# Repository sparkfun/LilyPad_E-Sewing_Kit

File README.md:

Lilypad E-Sewing ProtoSnap
====================

<table class="table table-hover table-striped table-bordered">
  <tr>
   <td><a href="https://www.sparkfun.com/products/14546"><div align="center"></div></a></center></td>
   <td><a href="https://www.sparkfun.com/products/14528"><div align="center"></div></a></td>
  </tr>
  <tr>
    <td><div align="center">LilyPad E-Sewing ProtoSnap [<a href="https://www.sparkfun.com/products/14546">DEV-14546</a>]</div></td>
    <td><div align="center">LilyPad E-Sewing ProtoSnap Kit [<a href="https://www.sparkfun.com/products/14528">KIT-14528</a>]</div></td>
  </tr>
</table>

The LilyPad E-Sewing ProtoSnap is a great way to explore how buttons and switches behave in simple e-sewing circuits before crafting your project. It comes pre-wired so you can plug in a battery and use the switch and button to turn the LEDs on and off. 

Repository Contents
-------------------
* **/Hardware** - All Eagle design files (.brd, .sch)
* **/Production** - Production panel files (.brd)

Documentation
--------------
* **[Hookup Guide](https://learn.sparkfun.com/tutorials/lilypad-e-sewing-protosnap-hookup-guide)** - Basic hookup guide for the E-Sewing ProtoSnap.

Version History
---------------
* [Hw-v15](https://github.com/sparkfun/LilyPad_E-Sewing_Kit/releases/tag/Hw-v15) - Version 15. Currently available.
* [Hw-v13](https://github.com/sparkfun/LilyPad_E-Sewing_Kit/releases/tag/Hw-v13) - Version 13. (Retired)

Product Versions
----------------
* [DEV-14546](https://www.sparkfun.com/products/14546) - LilyPad E-Sewing ProtoSnap
* [KIT-14528](https://www.sparkfun.com/products/14528) - LilyPad E-Sewing ProtoSnap Kit
* [DEV-11032](https://www.sparkfun.com/products/11032) - ProtoSnap LilyPad E-Sewing Kit (v13 Retired)
* [RTL-11051](https://www.sparkfun.com/products/11051) - Retail packaging of LilyPad E-Sewing Kit (Retired)
* [DEV-10964](https://www.sparkfun.com/products/retired/10964) - ProtoSnap - LilyPad E-Sewing Kit (v11 Retired)

License Information
-------------------
The hardware is released under [Creative Commons Share-alike 3.0](http://creativecommons.org/licenses/by-sa/3.0/).

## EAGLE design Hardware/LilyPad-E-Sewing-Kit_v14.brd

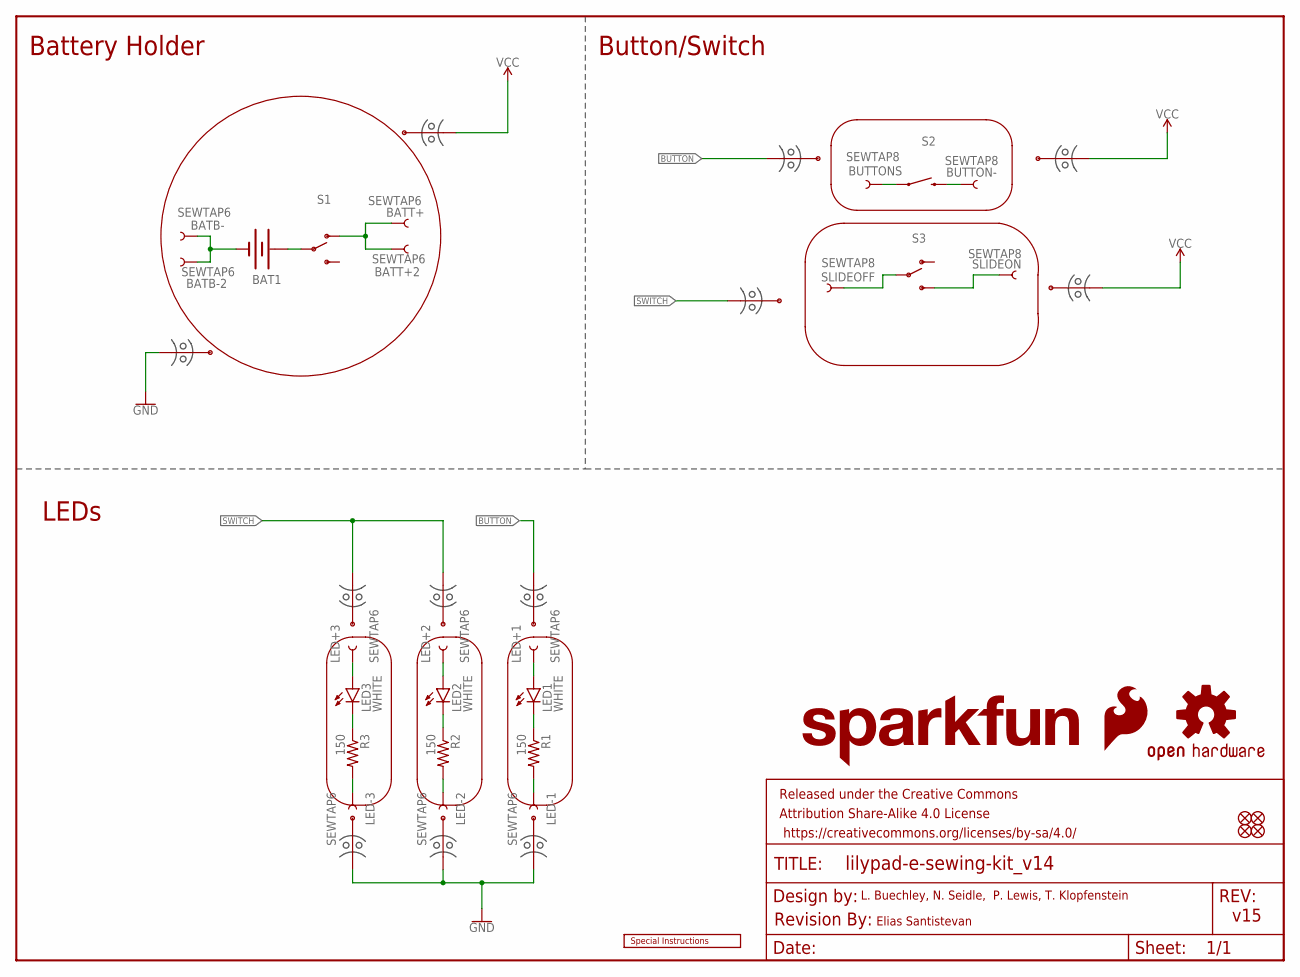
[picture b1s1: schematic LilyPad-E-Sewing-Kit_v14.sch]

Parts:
BAT1: 20mm coincell; BATTCON_20MM_4LEGS
BATB-, BATB-2: SEWTAP6; PETAL-SMALL-2SIDE
BATT+, BATT+2: SEWTAP6; PETAL-SMALL-2SIDE
BUTTON-: SEWTAP8; PETAL-MEDIUM-2SIDE
BUTTONS: SEWTAP8; PETAL-MEDIUM-2SIDE
FD1, FD2, FD3, FD4: FIDUCIALUFIDUCIAL; MICRO-FIDUCIAL
FRAME1: FRAME-LETTER; CREATIVE_COMMONS
LED1, LED2, LED3: WHITE; LED-1206
LED+1, LED+2, LED+3: SEWTAP6; PETAL-SMALL-2SIDE
LED-1, LED-2, LED-3: SEWTAP6; PETAL-SMALL-2SIDE
LOGO1: SFE_LOGO_FLAME.1_INCH; SFE_LOGO_FLAME_.1
LOGO2: OSHW-LOGOS; OSHW-LOGO-S
LOGO3: SFE_LOGO_NAME.1_INCH; SFE_LOGO_NAME_.1
MB1, MB2, MB3, MB4, MB5, MB6, MB7, MB8, MB9, MB10: MOUSE-BITE-12_HOLES; MOUST-BITE-1-(2_HOLES)
MB+: MOUSE-BITE-12_HOLES; MOUST-BITE-1-(2_HOLES)
MB-: MOUSE-BITE-12_HOLES; MOUST-BITE-1-(2_HOLES)
R1, R2, R3: 150; 0603-RES
S1: S1; AYZ0202
S2: SWITCH-MOMENTARY-2SMD; TACTILE-SWITCH-SMD
S3: S3; AYZ0202
SLIDEOFF: SEWTAP8; PETAL-MEDIUM-2SIDE
SLIDEON: SEWTAP8; PETAL-MEDIUM-2SIDE
U$1: REVISION
U$9: SPECIAL_INSTRUCTIONS-ORDERING; ORDERING_INSTRUCTIONS

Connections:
BUTTON: BUTTONS.1, LED1.A, LED+1.1, MB3.P$1, MB9.P$1, S2.1
GND: BAT1.NEGATIVE (-), BATB-.1, BATB-2.1, LED-1.1, LED-2.1, LED-3.1, MB6.P$1, MB7.P$1, MB8.P$1, MB-.P$1, R1.2, R2.2, R3.2
unnamed: BAT1.POSITIVE@1 (+), BAT1.POSITIVE@2 (+), BAT1.POSITIVE@3 (+), BAT1.POSITIVE@4 (+), S1.2
unnamed: LED1.C, R1.1
unnamed: LED2.C, R2.1
unnamed: LED3.C, R3.1
SWITCH: LED2.A, LED3.A, LED+2.1, LED+3.1, MB4.P$1, MB5.P$1, MB10.P$1, S3.2, SLIDEOFF.1
VCC: BATT+.1, BATT+2.1, BUTTON-.1, MB1.P$1, MB2.P$1, MB+.P$1, S1.1 (O), S2.3 (2), S3.3 (S), SLIDEON.1

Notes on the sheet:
L. Buechley, N. Seidle, P. Lewis, T. Klopfenstein
v15
Elias Santistevan
Button/Switch
Battery Holder
LEDs

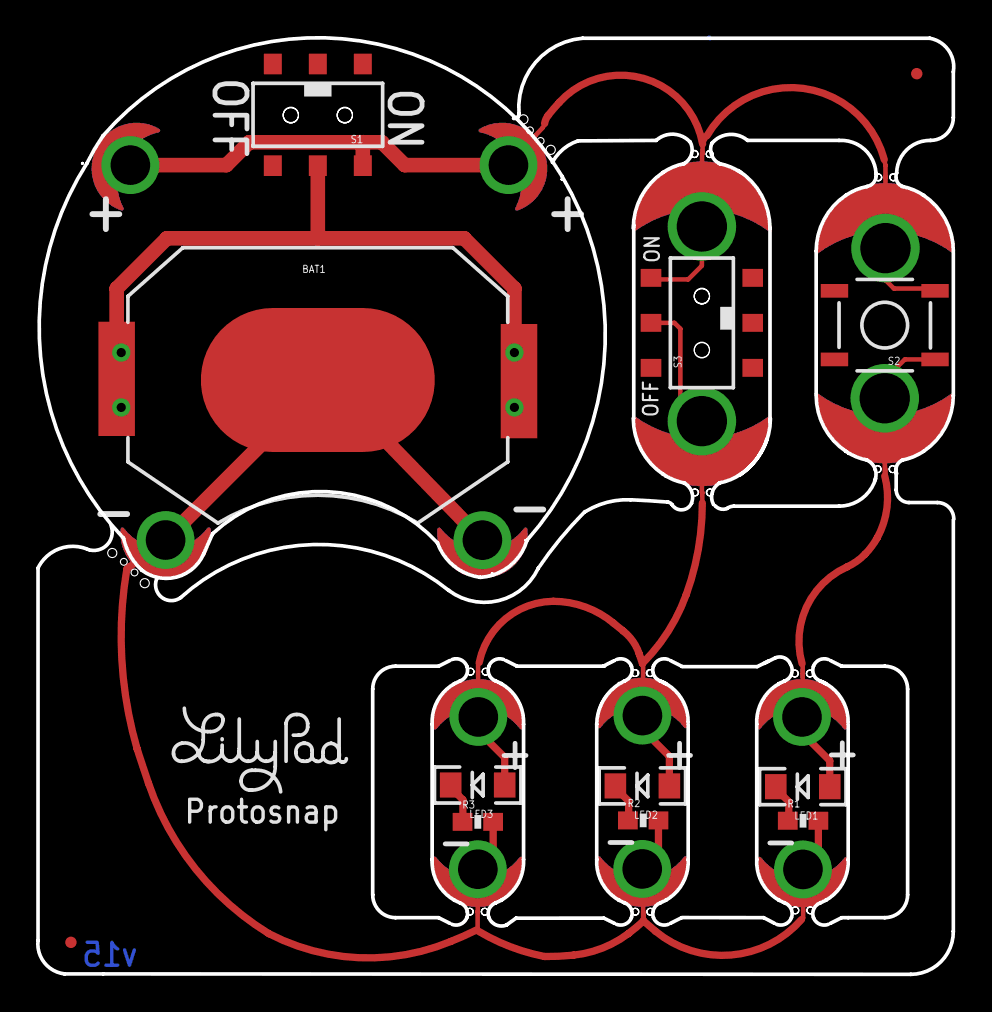
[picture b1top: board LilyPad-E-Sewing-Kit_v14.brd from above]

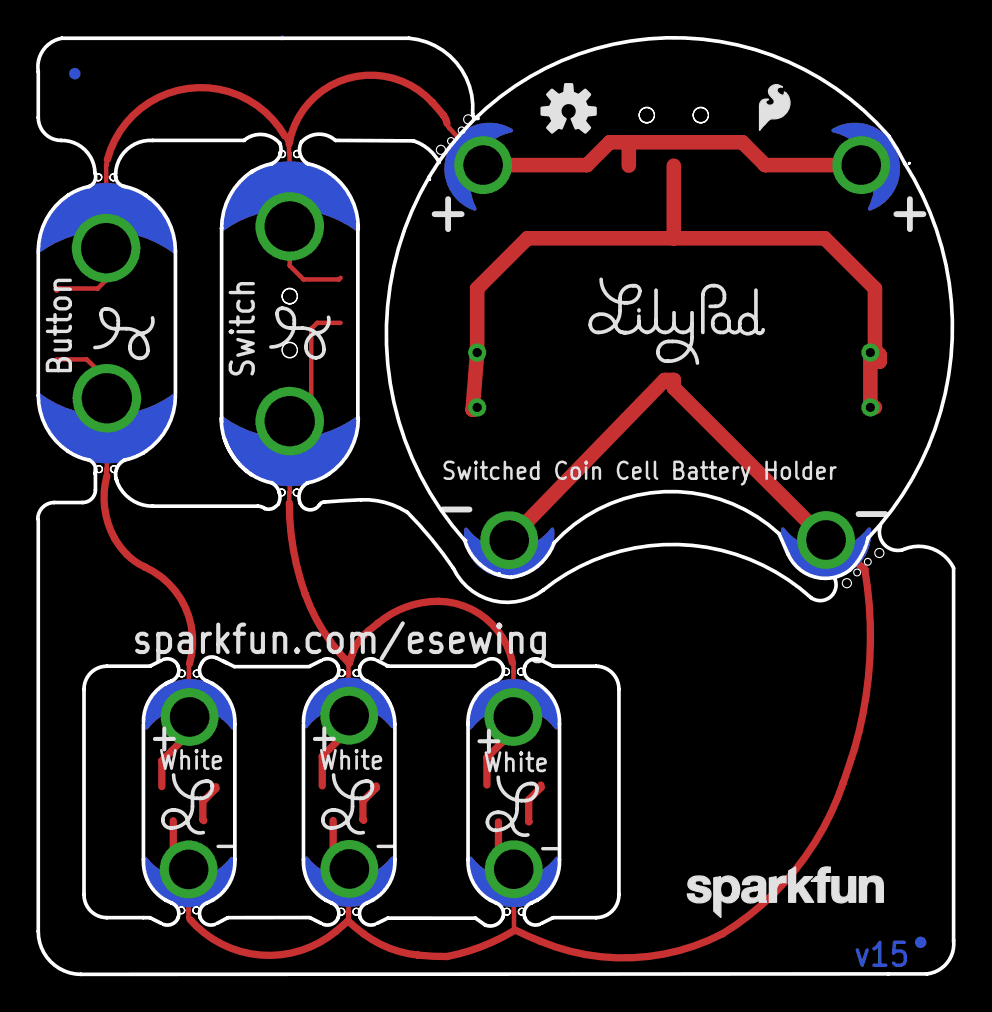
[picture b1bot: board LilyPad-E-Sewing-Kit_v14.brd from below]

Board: 2 copper layers, 50.9 x 52.0 mm, 53 parts (23 on the bottom side), 8 nets.

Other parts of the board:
U$2, U$3: LOGO-LILYPAD
U$4, U$5, U$6, U$7, U$8: LOGO-L

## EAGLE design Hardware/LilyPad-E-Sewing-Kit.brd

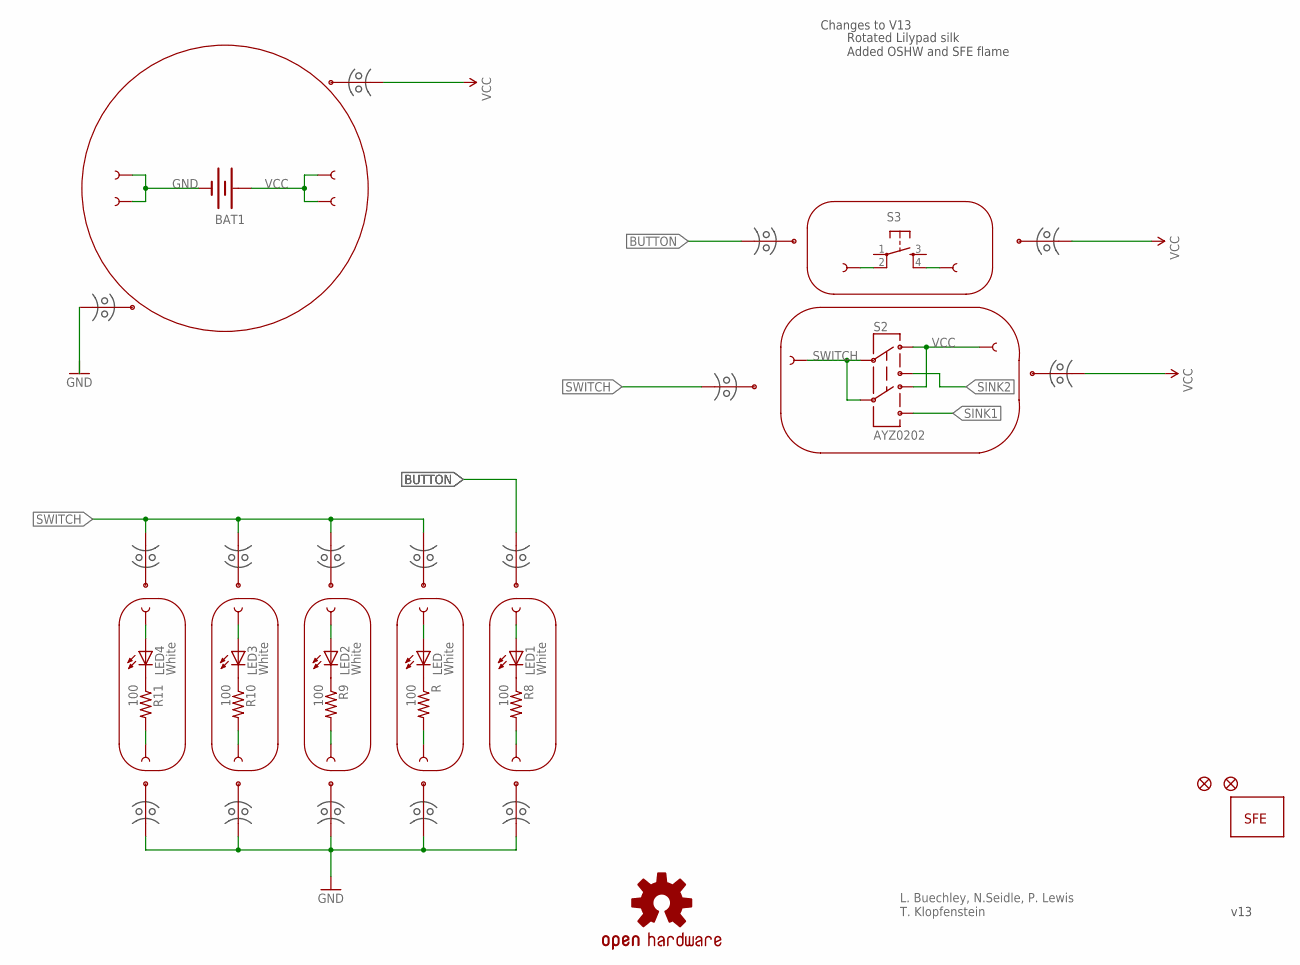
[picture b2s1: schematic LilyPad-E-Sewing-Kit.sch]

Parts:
BAT1: BATTERYBATTCON_20MM_4LEGS; BATTCON_20MM_4LEGS
BUTTON-: SEWTAP8; PETAL-SMALL
BUTTONS: SEWTAP8; PETAL-SMALL
JP1, JP4: FIDUCIAL1X2; FIDUCIAL-1X2
JP2: LOGO-SFESK; SFE-LOGO-FLAME
LED, LED1, LED2, LED3, LED4: White; LED-1206
LED+, LED+1, LED+2, LED+3, LED+4: SEWTAP6; PETAL-SMALL-2SIDE
LED-, LED-1, LED-2, LED-3, LED-4: SEWTAP6; PETAL-SMALL-2SIDE
R, R8, R9, R10, R11: 100; 0603-RES
S2: AYZ0202
S3: TAC_SWITCHSMD; TACTILE_SWITCH_SMD
SLIDEOFF: SEWTAP8; PETAL-SMALL
SLIDEON: SEWTAP8; PETAL-SMALL
U$1, U$2, U$3, U$4: SEWTAP6; PETAL-SMALL-2SIDE
U$6, U$7, U$10, U$11, U$12, U$13, U$14, U$15, U$16, U$17, U$18, U$19, U$40, U$42, U$44, U$46: MOUSE-BITE-12_HOLES; MOUST-BITE-1-(2_HOLES)
U$8: OSHW-LOGOS; OSHW-LOGO-S

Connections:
BUTTON: BUTTONS.1, LED1.A, LED+1.1, S3.2, U$13.P$1, U$42.P$1
GND: BAT1.2 (-), LED-.1, LED-1.1, LED-2.1, LED-3.1, LED-4.1, R.2, R8.2, R9.2, R10.2, R11.2, U$1.1, U$3.1, U$7.P$1, U$15.P$1, U$16.P$1, U$17.P$1, U$18.P$1, U$19.P$1
unnamed: LED.C, R.1
unnamed: LED1.C, R8.1
unnamed: LED2.C, R9.1
unnamed: LED3.C, R10.1
unnamed: LED4.C, R11.1
SINK1: S2.4 (6)
SINK2: S2.1 (3)
SWITCH: LED.A, LED2.A, LED3.A, LED4.A, LED+.1, LED+2.1, LED+3.1, LED+4.1, S2.2, S2.5, SLIDEOFF.1, U$10.P$1, U$11.P$1, U$12.P$1, U$14.P$1, U$44.P$1
VCC: BAT1.1 (+), BUTTON-.1, S2.3 (1), S2.6 (4), S3.4, SLIDEON.1, U$2.1, U$4.1, U$6.P$1, U$40.P$1, U$46.P$1

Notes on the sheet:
L. Buechley, N.Seidle, P. Lewis T. Klopfenstein
Changes to V13
Rotated Lilypad silk Added OSHW and SFE flame
v13

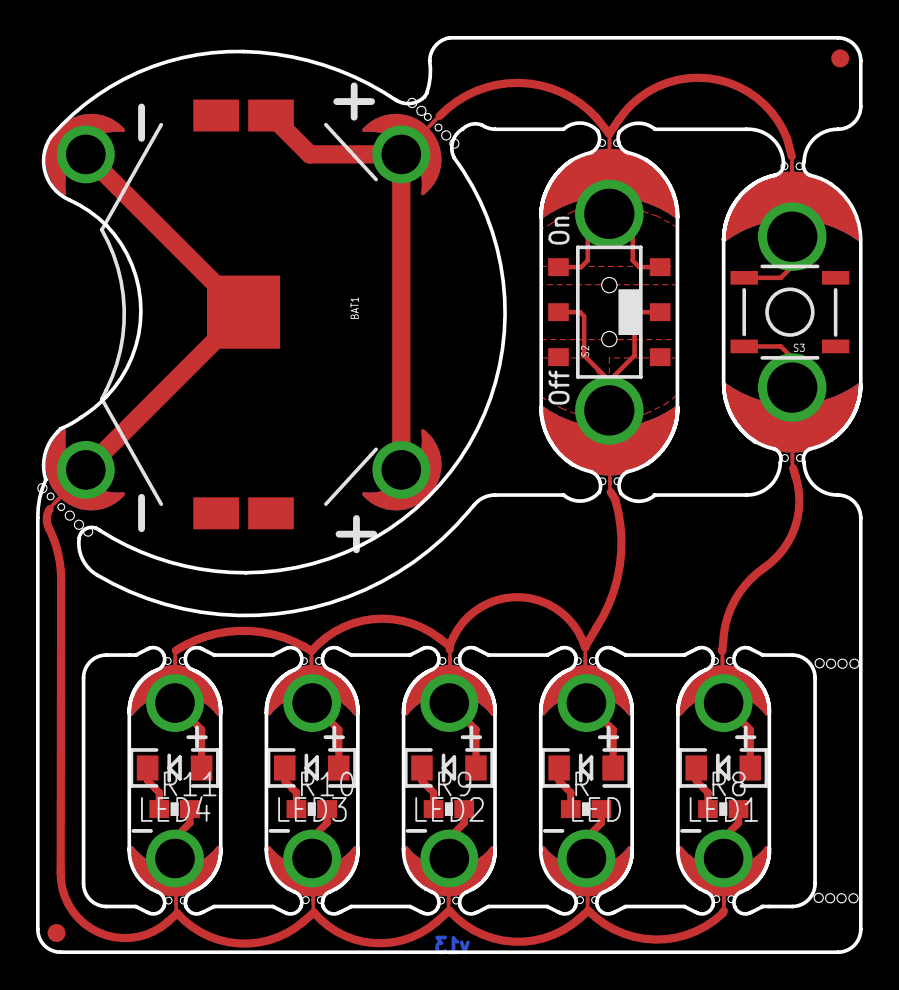
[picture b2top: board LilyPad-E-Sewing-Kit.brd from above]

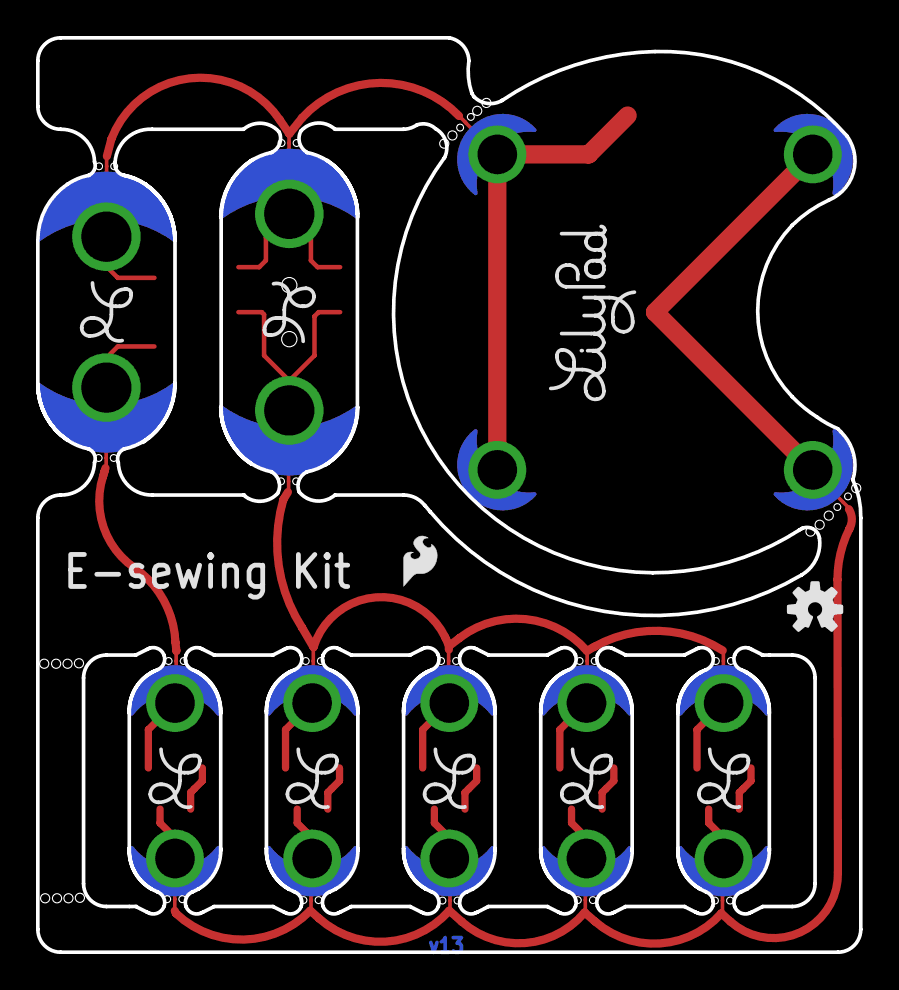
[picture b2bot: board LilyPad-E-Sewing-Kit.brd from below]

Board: 2 copper layers, 45.7 x 50.8 mm, 60 parts (26 on the bottom side), 9 nets.

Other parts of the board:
LOGO1, LOGO2, LOGO3, LOGO4, LOGO5, LOGO6, LOGO7: LOGO-LPL; LOGO-L
U$5: LOGO-LPLP; LOGO-LILYPAD
U$9: CREATIVE_COMMONS

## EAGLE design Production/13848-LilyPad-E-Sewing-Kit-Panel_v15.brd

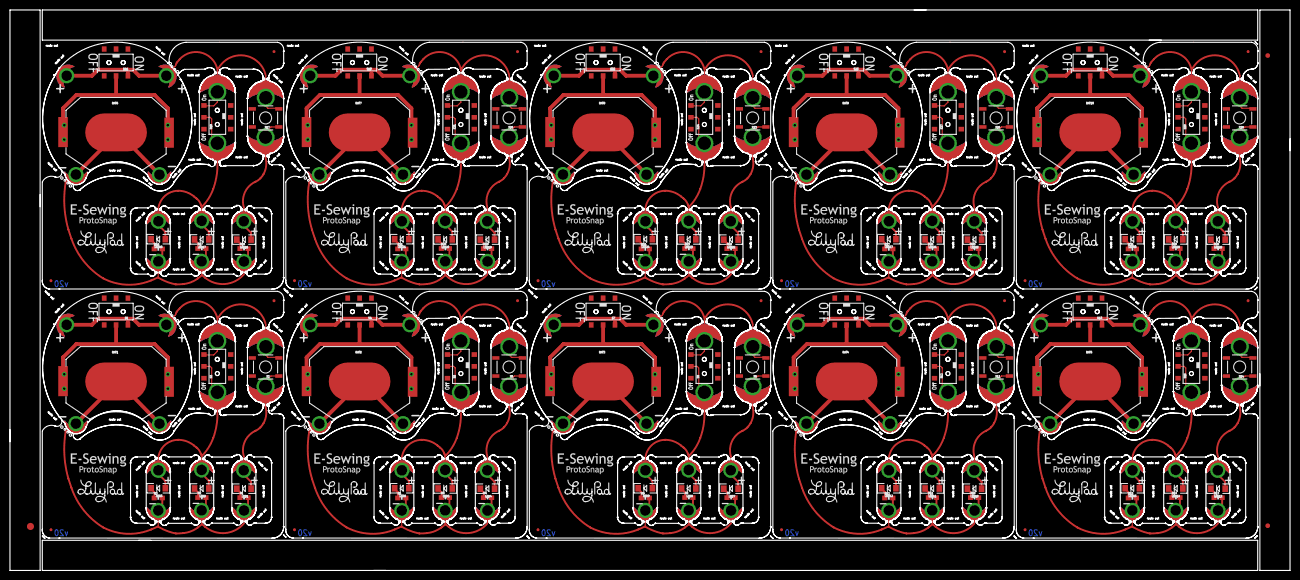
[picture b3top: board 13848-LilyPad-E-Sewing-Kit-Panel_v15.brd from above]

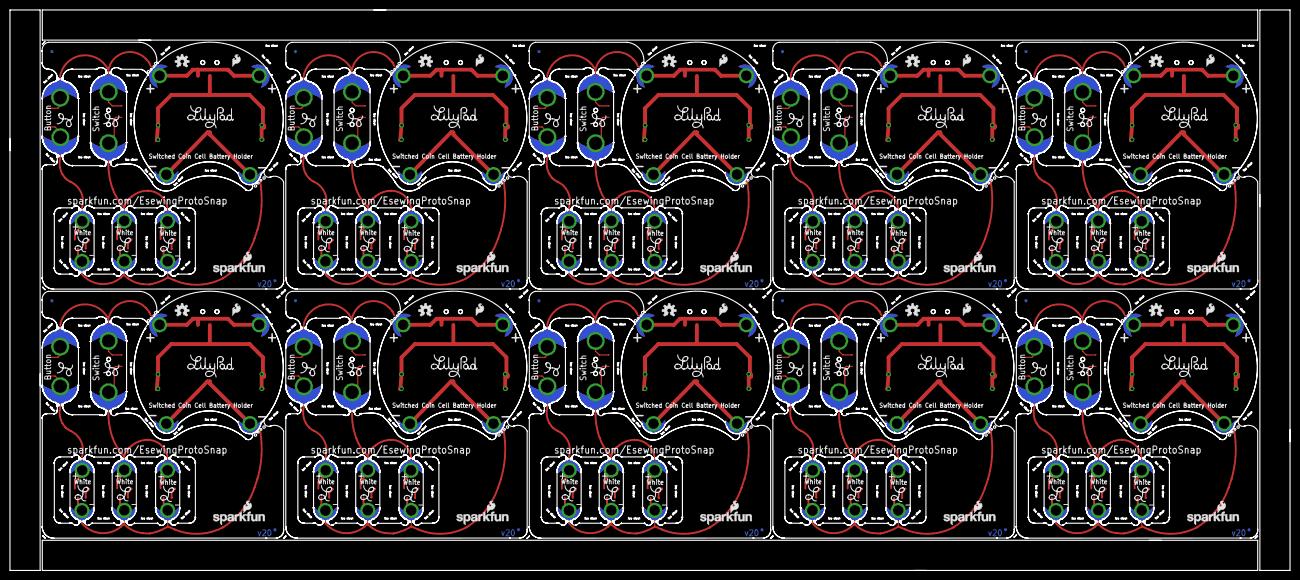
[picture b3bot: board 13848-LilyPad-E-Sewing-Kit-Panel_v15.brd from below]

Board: 2 copper layers, 269.7 x 118.1 mm, 503 parts (230 on the bottom side), 80 nets.

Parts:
BAT1, BAT2, BAT3, BAT4, BAT5, BAT6, BAT7, BAT8, BAT9, BAT10: 20mm coincell; BATTCON_20MM_4LEGS
BATB-, BATB-1, BATB-2, BATB-3, BATB-4, BATB-5, BATB-6, BATB-7, BATB-8, BATB-9, BATB-10, BATB-11, BATB-12, BATB-13, BATB-14, BATB-15, BATB-16, BATB-17, BATB-18, BATB-19: SEWTAP6; PETAL-SMALL-2SIDE
BATT+, BATT+1, BATT+2, BATT+3, BATT+4, BATT+5, BATT+6, BATT+7, BATT+8, BATT+9, BATT+10, BATT+11, BATT+12, BATT+13, BATT+14, BATT+15, BATT+16, BATT+17, BATT+18, BATT+19: SEWTAP6; PETAL-SMALL-2SIDE
BUTTON-, BUTTON-1, BUTTON-2, BUTTON-3, BUTTON-4, BUTTON-5, BUTTON-6, BUTTON-7, BUTTON-8, BUTTON-9: SEWTAP8; PETAL-MEDIUM-2SIDE
BUTTONS, BUTTONS1, BUTTONS2, BUTTONS3, BUTTONS4, BUTTONS5, BUTTONS6, BUTTONS7, BUTTONS8, BUTTONS9: SEWTAP8; PETAL-MEDIUM-2SIDE
E$1: FIDUCIAL-1.5X3
E$3, E$4: FIDUCIAL-1X2
FD1, FD2, FD3, FD4, FD5, FD6, FD7, FD8, FD9, FD10, FD11, FD12, FD13, FD14, FD15, FD16, FD17, FD18, FD19, FD20, FD21, FD22, FD23, FD24, FD25, FD26, FD27, FD28, FD29, FD30, FD31, FD32, FD33, FD34, FD35, FD36, FD37, FD38, FD39, FD40: FIDUCIALUFIDUCIAL; MICRO-FIDUCIAL
LED1, LED2, LED3, LED4, LED5, LED6, LED7, LED8, LED9, LED10, LED11, LED12, LED13, LED14, LED15, LED16, LED17, LED18, LED19, LED20, LED21, LED22, LED23, LED24, LED25, LED26, LED27, LED28, LED29, LED30: WHITE; LED-1206
LED+1, LED+2, LED+3, LED+4, LED+5, LED+6, LED+7, LED+8, LED+9, LED+10, LED+11, LED+12, LED+13, LED+14, LED+15, LED+16, LED+17, LED+18, LED+19, LED+20, LED+21, LED+22, LED+23, LED+24, LED+25, LED+26, LED+27, LED+28, LED+29, LED+30: SEWTAP6; PETAL-SMALL-2SIDE
LED-1, LED-2, LED-3, LED-4, LED-5, LED-6, LED-7, LED-8, LED-9, LED-10, LED-11, LED-12, LED-13, LED-14, LED-15, LED-16, LED-17, LED-18, LED-19, LED-20, LED-21, LED-22, LED-23, LED-24, LED-25, LED-26, LED-27, LED-28, LED-29, LED-30: SEWTAP6; PETAL-SMALL-2SIDE
LOGO1, LOGO4, LOGO7, LOGO10, LOGO13, LOGO16, LOGO19, LOGO22, LOGO25, LOGO28: SFE_LOGO_FLAME.1_INCH; SFE_LOGO_FLAME_.1
LOGO2, LOGO5, LOGO8, LOGO11, LOGO14, LOGO17, LOGO20, LOGO23, LOGO26, LOGO29: OSHW-LOGOS; OSHW-LOGO-S
LOGO3, LOGO6, LOGO9, LOGO12, LOGO15, LOGO18, LOGO21, LOGO24, LOGO27, LOGO30: SFE_LOGO_NAME_FLAME.1_INCH; SFE_LOGO_NAME_FLAME_.1
MB1, MB2, MB3, MB4, MB5, MB6, MB7, MB8, MB9, MB10, MB11, MB12, MB13, MB14, MB15, MB16, MB17, MB18, MB19, MB20, MB21, MB22, MB23, MB24, MB25, MB26, MB27, MB28, MB29, MB30, MB31, MB32, MB33, MB34, MB35, MB36, MB37, MB38, MB39, MB40, MB41, MB42, MB43, MB44, MB45, MB46, MB47, MB48, MB49, MB50, MB51, MB52, MB53, MB54, MB55, MB56, MB57, MB58, MB59, MB60, MB61, MB62, MB63, MB64, MB65, MB66, MB67, MB68, MB69, MB70, MB71, MB72, MB73, MB74, MB75, MB76, MB77, MB78, MB79, MB80, MB81, MB82, MB83, MB84, MB85, MB86, MB87, MB88, MB89, MB90, MB91, MB92, MB93, MB94, MB95, MB96, MB97, MB98, MB99, MB100: MOUSE-BITE-12_HOLES; MOUST-BITE-1-(2_HOLES)
MB+, MB+1, MB+2, MB+3, MB+4, MB+5, MB+6, MB+7, MB+8, MB+9: MOUSE-BITE-12_HOLES; MOUST-BITE-1-(2_HOLES)
MB-, MB-1, MB-2, MB-3, MB-4, MB-5, MB-6, MB-7, MB-8, MB-9: MOUSE-BITE-12_HOLES; MOUST-BITE-1-(2_HOLES)
R1, R2, R3, R4, R5, R6, R7, R8, R9, R10, R11, R12, R13, R14, R15, R16, R17, R18, R19, R20, R21, R22, R23, R24, R25, R26, R27, R28, R29, R30: 150; 0603-RES
S1, S4, S7, S10, S13, S16, S19, S22, S25, S28: S1; AYZ0202
S2, S5, S8, S11, S14, S17, S20, S23, S26, S29: SWITCH-MOMENTARY-2SMD; TACTILE-SWITCH-SMD
S3, S6, S9, S12, S15, S18, S21, S24, S27, S30: S3; AYZ0202
SLIDEOFF, SLIDEOFF1, SLIDEOFF2, SLIDEOFF3, SLIDEOFF4, SLIDEOFF5, SLIDEOFF6, SLIDEOFF7, SLIDEOFF8, SLIDEOFF9: SEWTAP8; PETAL-MEDIUM-2SIDE
SLIDEON, SLIDEON1, SLIDEON2, SLIDEON3, SLIDEON4, SLIDEON5, SLIDEON6, SLIDEON7, SLIDEON8, SLIDEON9: SEWTAP8; PETAL-MEDIUM-2SIDE
U$1, U$2, U$3, U$9, U$15, U$16, U$22, U$23, U$29, U$30, U$36, U$37, U$43, U$44, U$50, U$51, U$57, U$58, U$64, U$65: LOGO-LILYPAD
U$4, U$5, U$6, U$7, U$8, U$10, U$11, U$12, U$13, U$14, U$17, U$18, U$19, U$20, U$21, U$24, U$25, U$26, U$27, U$28, U$31, U$32, U$33, U$34, U$35, U$38, U$39, U$40, U$41, U$42, U$45, U$46, U$47, U$48, U$49, U$52, U$53, U$54, U$55, U$56, U$59, U$60, U$61, U$62, U$63, U$66, U$67, U$68, U$69, U$70: LOGO-L

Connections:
BUTTON: BUTTONS.1, LED1.A, LED+1.1, MB3.P$1, MB9.P$1, S2.1
BUTTON1: BUTTONS1.1, LED4.A, LED+4.1, MB14.P$1, MB20.P$1, S5.1
BUTTON2: BUTTONS2.1, LED7.A, LED+7.1, MB24.P$1, MB30.P$1, S8.1
BUTTON3: BUTTONS3.1, LED10.A, LED+10.1, MB34.P$1, MB40.P$1, S11.1
BUTTON4: BUTTONS4.1, LED13.A, LED+13.1, MB44.P$1, MB50.P$1, S14.1
BUTTON5: BUTTONS5.1, LED16.A, LED+16.1, MB54.P$1, MB60.P$1, S17.1
BUTTON6: BUTTONS6.1, LED19.A, LED+19.1, MB64.P$1, MB70.P$1, S20.1
BUTTON7: BUTTONS7.1, LED22.A, LED+22.1, MB74.P$1, MB80.P$1, S23.1
BUTTON8: BUTTONS8.1, LED25.A, LED+25.1, MB84.P$1, MB90.P$1, S26.1
BUTTON9: BUTTONS9.1, LED28.A, LED+28.1, MB94.P$1, MB100.P$1, S29.1
GND: BAT1.NEGATIVE, BATB-.1, BATB-2.1, LED-1.1, LED-2.1, LED-3.1, MB6.P$1, MB7.P$1, MB8.P$1, MB-.P$1, R1.2, R2.2, R3.2
GND1: BAT2.NEGATIVE, BATB-1.1, BATB-3.1, LED-4.1, LED-5.1, LED-6.1, MB17.P$1, MB18.P$1, MB19.P$1, MB-1.P$1, R4.2, R5.2, R6.2
GND2: BAT3.NEGATIVE, BATB-4.1, BATB-5.1, LED-7.1, LED-8.1, LED-9.1, MB27.P$1, MB28.P$1, MB29.P$1, MB-2.P$1, R7.2, R8.2, R9.2
GND3: BAT4.NEGATIVE, BATB-6.1, BATB-7.1, LED-10.1, LED-11.1, LED-12.1, MB37.P$1, MB38.P$1, MB39.P$1, MB-3.P$1, R10.2, R11.2, R12.2
GND4: BAT5.NEGATIVE, BATB-8.1, BATB-9.1, LED-13.1, LED-14.1, LED-15.1, MB47.P$1, MB48.P$1, MB49.P$1, MB-4.P$1, R13.2, R14.2, R15.2
GND5: BAT6.NEGATIVE, BATB-10.1, BATB-11.1, LED-16.1, LED-17.1, LED-18.1, MB57.P$1, MB58.P$1, MB59.P$1, MB-5.P$1, R16.2, R17.2, R18.2
GND6: BAT7.NEGATIVE, BATB-12.1, BATB-13.1, LED-19.1, LED-20.1, LED-21.1, MB67.P$1, MB68.P$1, MB69.P$1, MB-6.P$1, R19.2, R20.2, R21.2
GND7: BAT8.NEGATIVE, BATB-14.1, BATB-15.1, LED-22.1, LED-23.1, LED-24.1, MB77.P$1, MB78.P$1, MB79.P$1, MB-7.P$1, R22.2, R23.2, R24.2
GND8: BAT9.NEGATIVE, BATB-16.1, BATB-17.1, LED-25.1, LED-26.1, LED-27.1, MB87.P$1, MB88.P$1, MB89.P$1, MB-8.P$1, R25.2, R26.2, R27.2
GND9: BAT10.NEGATIVE, BATB-18.1, BATB-19.1, LED-28.1, LED-29.1, LED-30.1, MB97.P$1, MB98.P$1, MB99.P$1, MB-9.P$1, R28.2, R29.2, R30.2
unnamed: BAT1.POSITIVE@1, BAT1.POSITIVE@2, BAT1.POSITIVE@3, BAT1.POSITIVE@4, S1.2
unnamed: BAT2.POSITIVE@1, BAT2.POSITIVE@2, BAT2.POSITIVE@3, BAT2.POSITIVE@4, S4.2
unnamed: LED4.C, R4.1
unnamed: LED5.C, R5.1
unnamed: LED6.C, R6.1
unnamed: BAT3.POSITIVE@1, BAT3.POSITIVE@2, BAT3.POSITIVE@3, BAT3.POSITIVE@4, S7.2
unnamed: LED7.C, R7.1
unnamed: LED8.C, R8.1
unnamed: LED1.C, R1.1
unnamed: LED2.C, R2.1
unnamed: LED3.C, R3.1
unnamed: LED9.C, R9.1
unnamed: BAT4.POSITIVE@1, BAT4.POSITIVE@2, BAT4.POSITIVE@3, BAT4.POSITIVE@4, S10.2
unnamed: LED10.C, R10.1
unnamed: LED11.C, R11.1
unnamed: LED12.C, R12.1
unnamed: BAT5.POSITIVE@1, BAT5.POSITIVE@2, BAT5.POSITIVE@3, BAT5.POSITIVE@4, S13.2
unnamed: LED13.C, R13.1
unnamed: LED14.C, R14.1
unnamed: LED15.C, R15.1
unnamed: BAT6.POSITIVE@1, BAT6.POSITIVE@2, BAT6.POSITIVE@3, BAT6.POSITIVE@4, S16.2
unnamed: LED16.C, R16.1
unnamed: LED17.C, R17.1
unnamed: LED18.C, R18.1
unnamed: BAT7.POSITIVE@1, BAT7.POSITIVE@2, BAT7.POSITIVE@3, BAT7.POSITIVE@4, S19.2
unnamed: LED19.C, R19.1
unnamed: LED20.C, R20.1
unnamed: LED21.C, R21.1
unnamed: BAT8.POSITIVE@1, BAT8.POSITIVE@2, BAT8.POSITIVE@3, BAT8.POSITIVE@4, S22.2
unnamed: LED22.C, R22.1
unnamed: LED23.C, R23.1
unnamed: LED24.C, R24.1
unnamed: BAT9.POSITIVE@1, BAT9.POSITIVE@2, BAT9.POSITIVE@3, BAT9.POSITIVE@4, S25.2
unnamed: LED25.C, R25.1
unnamed: LED26.C, R26.1
unnamed: LED27.C, R27.1
unnamed: BAT10.POSITIVE@1, BAT10.POSITIVE@2, BAT10.POSITIVE@3, BAT10.POSITIVE@4, S28.2
unnamed: LED28.C, R28.1
unnamed: LED29.C, R29.1
unnamed: LED30.C, R30.1
SWITCH: LED2.A, LED3.A, LED+2.1, LED+3.1, MB4.P$1, MB5.P$1, MB10.P$1, S3.2, SLIDEOFF.1
SWITCH1: LED5.A, LED6.A, LED+5.1, LED+6.1, MB12.P$1, MB15.P$1, MB16.P$1, S6.2, SLIDEOFF1.1
SWITCH2: LED8.A, LED9.A, LED+8.1, LED+9.1, MB22.P$1, MB25.P$1, MB26.P$1, S9.2, SLIDEOFF2.1
SWITCH3: LED11.A, LED12.A, LED+11.1, LED+12.1, MB32.P$1, MB35.P$1, MB36.P$1, S12.2, SLIDEOFF3.1
SWITCH4: LED14.A, LED15.A, LED+14.1, LED+15.1, MB42.P$1, MB45.P$1, MB46.P$1, S15.2, SLIDEOFF4.1
SWITCH5: LED17.A, LED18.A, LED+17.1, LED+18.1, MB52.P$1, MB55.P$1, MB56.P$1, S18.2, SLIDEOFF5.1
SWITCH6: LED20.A, LED21.A, LED+20.1, LED+21.1, MB62.P$1, MB65.P$1, MB66.P$1, S21.2, SLIDEOFF6.1
SWITCH7: LED23.A, LED24.A, LED+23.1, LED+24.1, MB72.P$1, MB75.P$1, MB76.P$1, S24.2, SLIDEOFF7.1
SWITCH8: LED26.A, LED27.A, LED+26.1, LED+27.1, MB82.P$1, MB85.P$1, MB86.P$1, S27.2, SLIDEOFF8.1
SWITCH9: LED29.A, LED30.A, LED+29.1, LED+30.1, MB92.P$1, MB95.P$1, MB96.P$1, S30.2, SLIDEOFF9.1
VCC: BATT+.1, BATT+2.1, BUTTON-.1, MB1.P$1, MB2.P$1, MB+.P$1, S1.1, S2.3, S3.3, SLIDEON.1
VCC1: BATT+1.1, BATT+3.1, BUTTON-1.1, MB11.P$1, MB13.P$1, MB+1.P$1, S4.1, S5.3, S6.3, SLIDEON1.1
VCC2: BATT+4.1, BATT+5.1, BUTTON-2.1, MB21.P$1, MB23.P$1, MB+2.P$1, S7.1, S8.3, S9.3, SLIDEON2.1
VCC3: BATT+6.1, BATT+7.1, BUTTON-3.1, MB31.P$1, MB33.P$1, MB+3.P$1, S10.1, S11.3, S12.3, SLIDEON3.1
VCC4: BATT+8.1, BATT+9.1, BUTTON-4.1, MB41.P$1, MB43.P$1, MB+4.P$1, S13.1, S14.3, S15.3, SLIDEON4.1
VCC5: BATT+10.1, BATT+11.1, BUTTON-5.1, MB51.P$1, MB53.P$1, MB+5.P$1, S16.1, S17.3, S18.3, SLIDEON5.1
VCC6: BATT+12.1, BATT+13.1, BUTTON-6.1, MB61.P$1, MB63.P$1, MB+6.P$1, S19.1, S20.3, S21.3, SLIDEON6.1
VCC7: BATT+14.1, BATT+15.1, BUTTON-7.1, MB71.P$1, MB73.P$1, MB+7.P$1, S22.1, S23.3, S24.3, SLIDEON7.1
VCC8: BATT+16.1, BATT+17.1, BUTTON-8.1, MB81.P$1, MB83.P$1, MB+8.P$1, S25.1, S26.3, S27.3, SLIDEON8.1
VCC9: BATT+18.1, BATT+19.1, BUTTON-9.1, MB91.P$1, MB93.P$1, MB+9.P$1, S28.1, S29.3, S30.3, SLIDEON9.1

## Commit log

2013-05-06 Initial file additions.
2013-05-07 Updated board files
2013-05-13 Fixed labeling on board.
2016-04-14 Updated files
2016-04-18 Updated board file
2016-04-18 Updated board and schemtic files
2016-04-18 Moved Mousebites
2016-04-18 Added PROD-IDs
2016-04-18 updated brd file
2016-04-18 Updated Resistor Value
2016-04-25 Updated Brd and Sch files (in Sync)
2016-04-25 Chnages per QC checklist
2016-04-26 updated brd files per QC
2016-04-26 Approved DRC Erros
2016-05-24 Updated schematic and board files --missing connection fixed
2016-06-07 Updated Board and Schematic files
2016-06-13 Updated brd and sch files per engineering design review 6/13/16
2016-06-13 Approved DRC errors
2016-06-13 Updated Brd File per QC checklist
2016-06-15 Updated brd file per QC
2016-06-21 created panel v14
2016-06-21 re-created panel v14
2017-10-11 Silk update for consistency amongst the Lilypad product line.
2017-10-12 Updated schematic
    Special Ordering Instructions, two more fiducials, dashed lines to
    dilineate parts along with labels amongst other minor changes.
2017-10-19 Final text object put into place
    "E-Sewing Protosnap" was added as silk according to dimension outlines
    specified in the Lilypad document provided by Lilypad Coordinator.
2017-10-23 Changed file names to reflect github branch.
2017-11-03 Updated website, capitalized teh "S" in ProtoSnap, and changed "OFF" and "ON"
2017-11-08 Put it back on grid....
2017-11-08 Revert "Put it back on grid...."
    This reverts commit 080445da69f31666997101091cdcd3686e199cd1.
2017-11-08 Picked a different grid....
2017-11-08 Las change did not commit, trying again.
2017-11-09 Created panel v15
2017-11-09 Changed file names
2017-12-07 Update README.md
    Add tutorial. Create tag for version history before updated.
2017-12-07 Update README.md
    Update for new product release.
2017-12-22 Update README.md
    Update Hookup Guide link to new tutorial in [learn.sparkfun.com](learn.sparkfun.com) .

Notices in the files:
parts and their libraries:
SparkFun-Aesthetics: Licensing: CC v3.0 Share-Alike You are welcome to use this library for commercial purposes.
SparkFun-Aesthetics: Released under the Creative Commons Attribution Share-Alike 3.0 License
SparkFun-Aesthetics: Released under the Creative Commons
